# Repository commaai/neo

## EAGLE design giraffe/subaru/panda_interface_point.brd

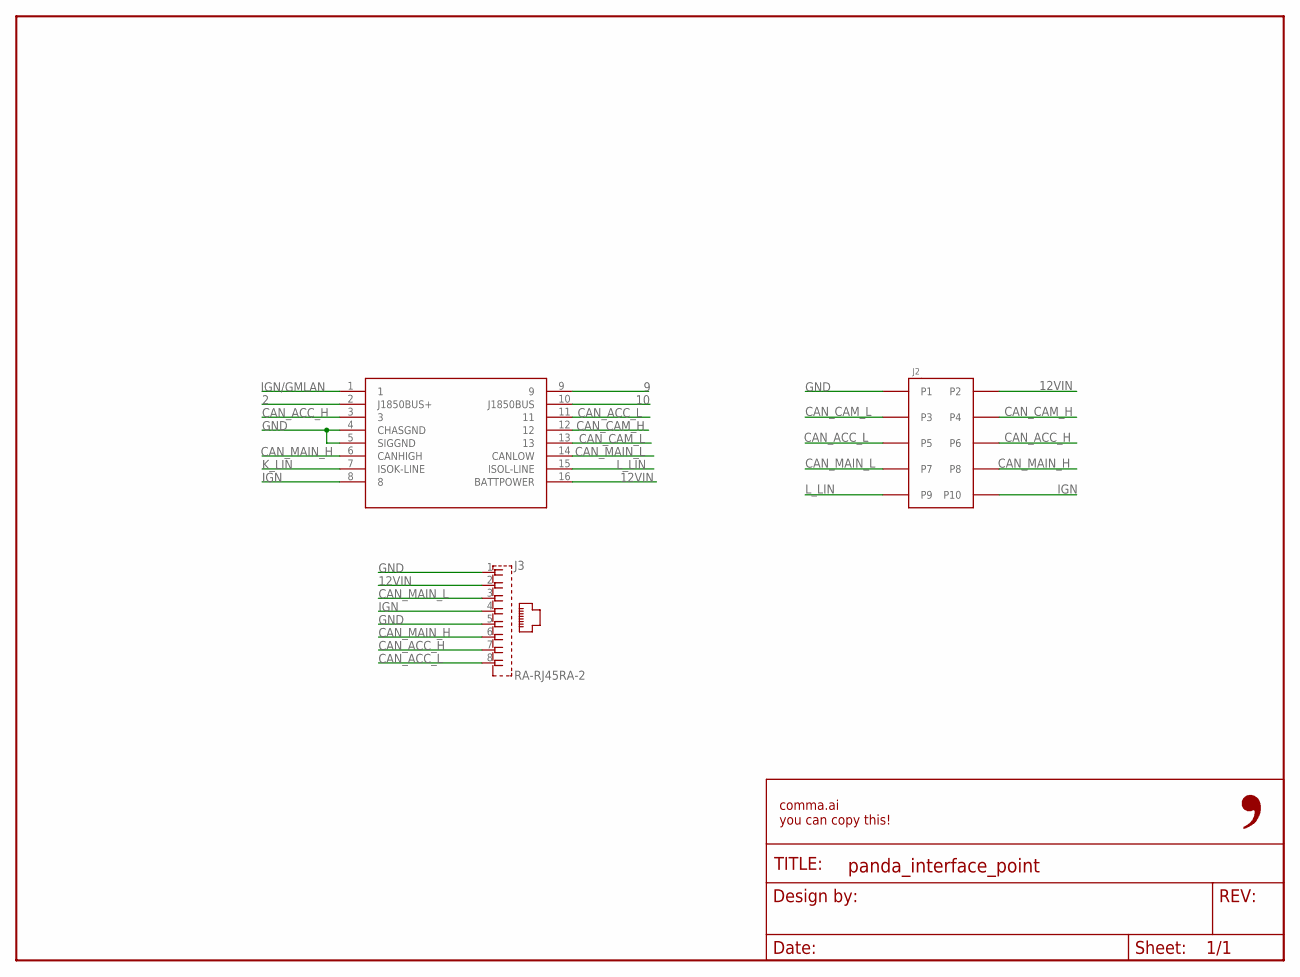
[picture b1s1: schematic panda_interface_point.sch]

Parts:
FRAME1: FRAME-LETTER-OPENNO_PACKAGE; DUMMY
J1: OBDII-FEMALE-CUT; OBDII-FEMALE-MIDCUT
J2: 5018761040
J3: RA-RJ45RA-2; RA-RJ45-2

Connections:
2: J1.2 (J1850BUS+)
9: J1.9
10: J1.10 (J1850BUS)
12VIN: J1.16 (BATTPOWER), J2.P2, J3.2
CAN_ACC_H: J1.3, J2.P6, J3.7
CAN_ACC_L: J1.11, J2.P5, J3.8
CAN_CAM_H: J1.12, J2.P4
CAN_CAM_L: J1.13, J2.P3
CAN_MAIN_H: J1.6 (CANHIGH), J2.P8, J3.6
CAN_MAIN_L: J1.14 (CANLOW), J2.P7, J3.3
GND: J1.4 (CHASGND), J1.5 (SIGGND), J2.P1, J3.1, J3.5
IGN: J1.8, J2.P10, J3.4
IGN/GMLAN: J1.1
K_LIN: J1.7 (ISOK-LINE)
L_LIN: J1.15 (ISOL-LINE), J2.P9

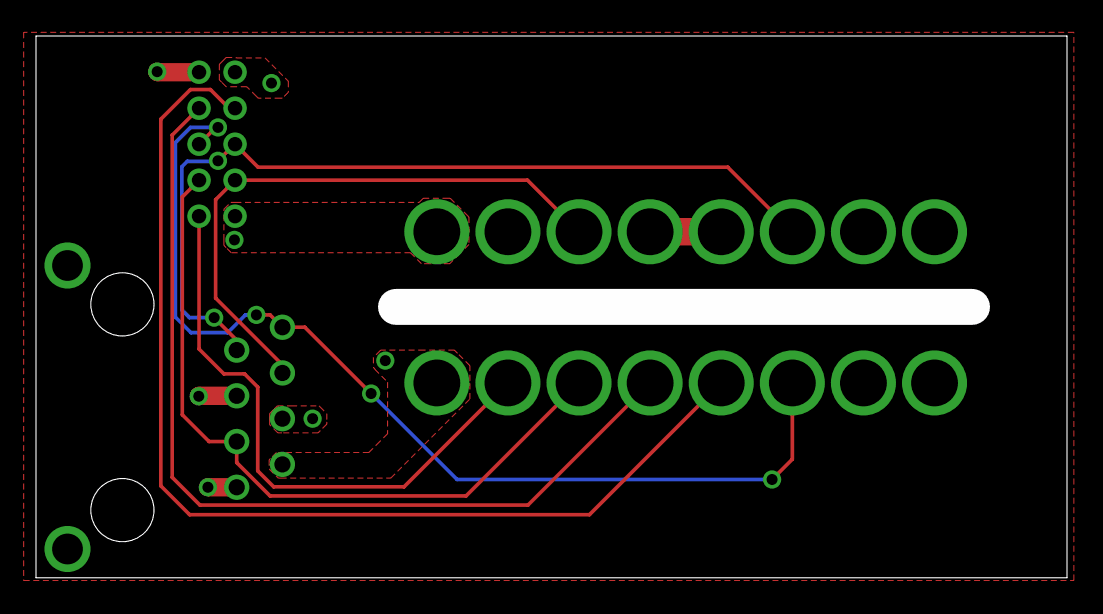
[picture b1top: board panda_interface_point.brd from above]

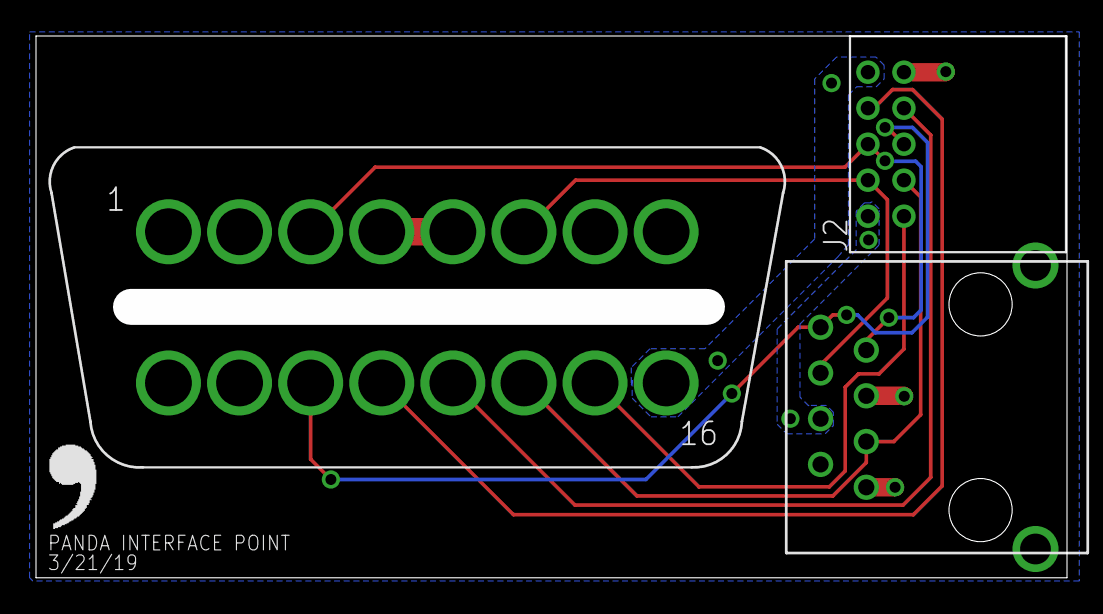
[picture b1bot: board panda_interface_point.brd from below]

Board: 2 copper layers, 57.3 x 30.1 mm, 5 parts (4 on the bottom side), 10 nets.

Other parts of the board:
U$1: LOGO

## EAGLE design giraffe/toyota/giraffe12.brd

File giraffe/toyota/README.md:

Toyota giraffe
====

Get your panda deeper into your compatible Toyota vehicle

The switches
====

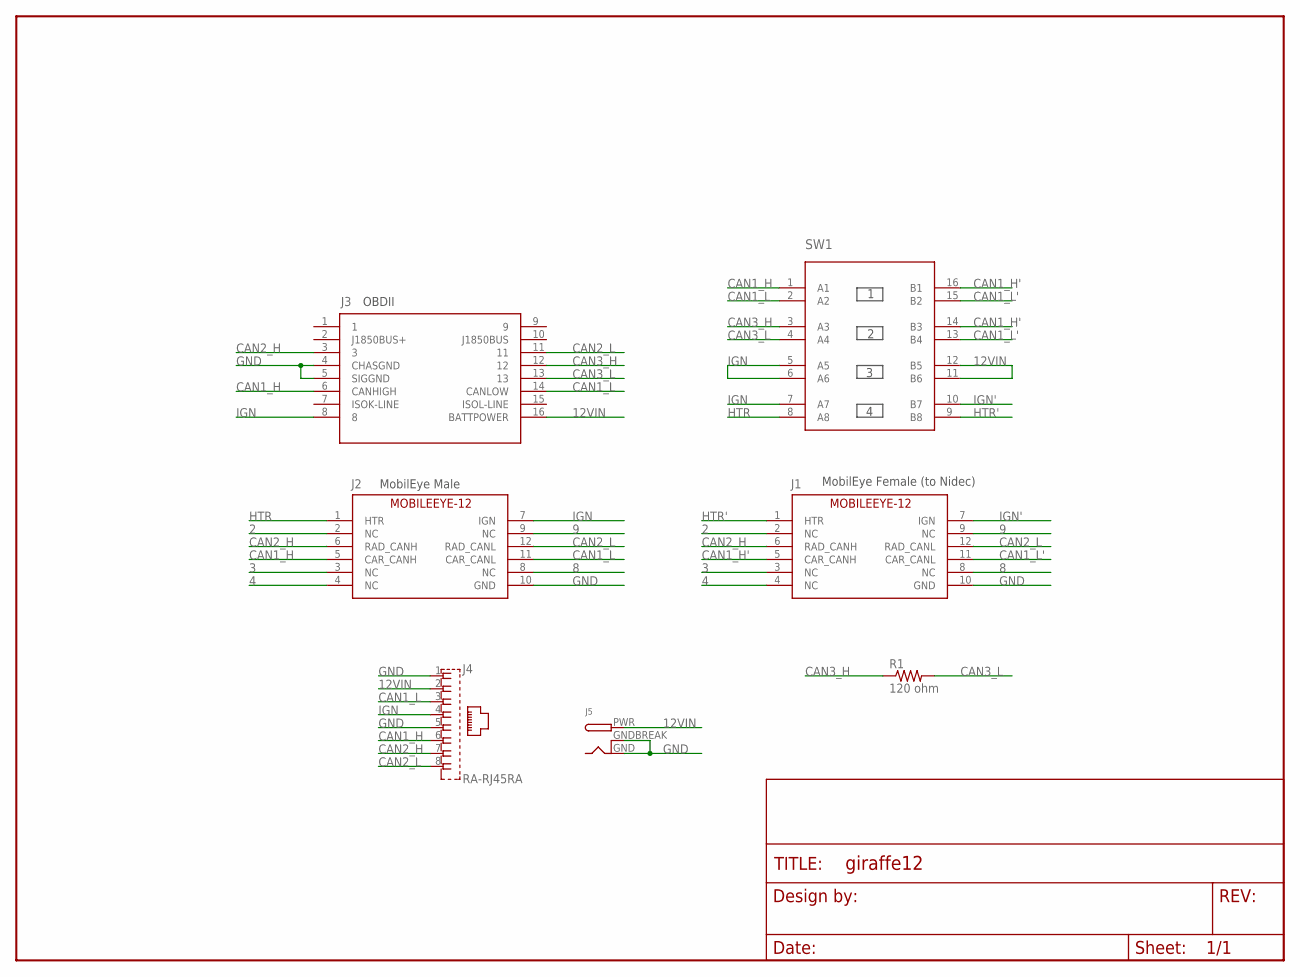
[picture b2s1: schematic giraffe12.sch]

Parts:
FRAME1: FRAME-LETTERNO_PACKAGE; DUMMY
J1: MOBILEEYE-12FEMALE; 2X6-TE-FEMALE
J2: MOBILEEYE-12MALE; 2X6-TE-RA
J3: OBDII-FEMALE-CUT; OBDII-FEMALE-MIDCUT
J4: RA-RJ45RA; RA-RJ45
J5: DCBARRELPTH; DCJACK_2MM_PTH
R1: 120 ohm; 0603-R
SW1: 4XDPSTSMT; 4-DPST

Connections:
2: J1.2 (NC), J2.2 (NC)
3: J1.3 (NC), J2.3 (NC)
4: J1.4 (NC), J2.4 (NC)
8: J1.8 (NC), J2.8 (NC)
9: J1.9 (NC), J2.9 (NC)
12VIN: J3.16 (BATTPOWER), J4.2, J5.PWR, SW1.11 (B6), SW1.12 (B5)
CAN1_H: J2.5 (CAR_CANH), J3.6 (CANHIGH), J4.6, SW1.1 (A1)
CAN1_H': J1.5 (CAR_CANH), SW1.14 (B3), SW1.16 (B1)
CAN1_L: J2.11 (CAR_CANL), J3.14 (CANLOW), J4.3, SW1.2 (A2)
CAN1_L': J1.11 (CAR_CANL), SW1.13 (B4), SW1.15 (B2)
CAN2_H: J1.6 (RAD_CANH), J2.6 (RAD_CANH), J3.3, J4.7
CAN2_L: J1.12 (RAD_CANL), J2.12 (RAD_CANL), J3.11, J4.8
CAN3_H: J3.12, R1.1, SW1.3 (A3)
CAN3_L: J3.13, R1.2, SW1.4 (A4)
GND: J1.10 (GND), J2.10 (GND), J3.4 (CHASGND), J3.5 (SIGGND), J4.1, J4.5, J5.GND, J5.GNDBREAK
HTR: J2.1 (HTR), SW1.8 (A8)
HTR': J1.1 (HTR), SW1.9 (B8)
IGN: J2.7 (IGN), J3.8, J4.4, SW1.5 (A5), SW1.6 (A6), SW1.7 (A7)
IGN': J1.7 (IGN), SW1.10 (B7)

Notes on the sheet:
OBDII
MobilEye Male
MobilEye Female (to Nidec)

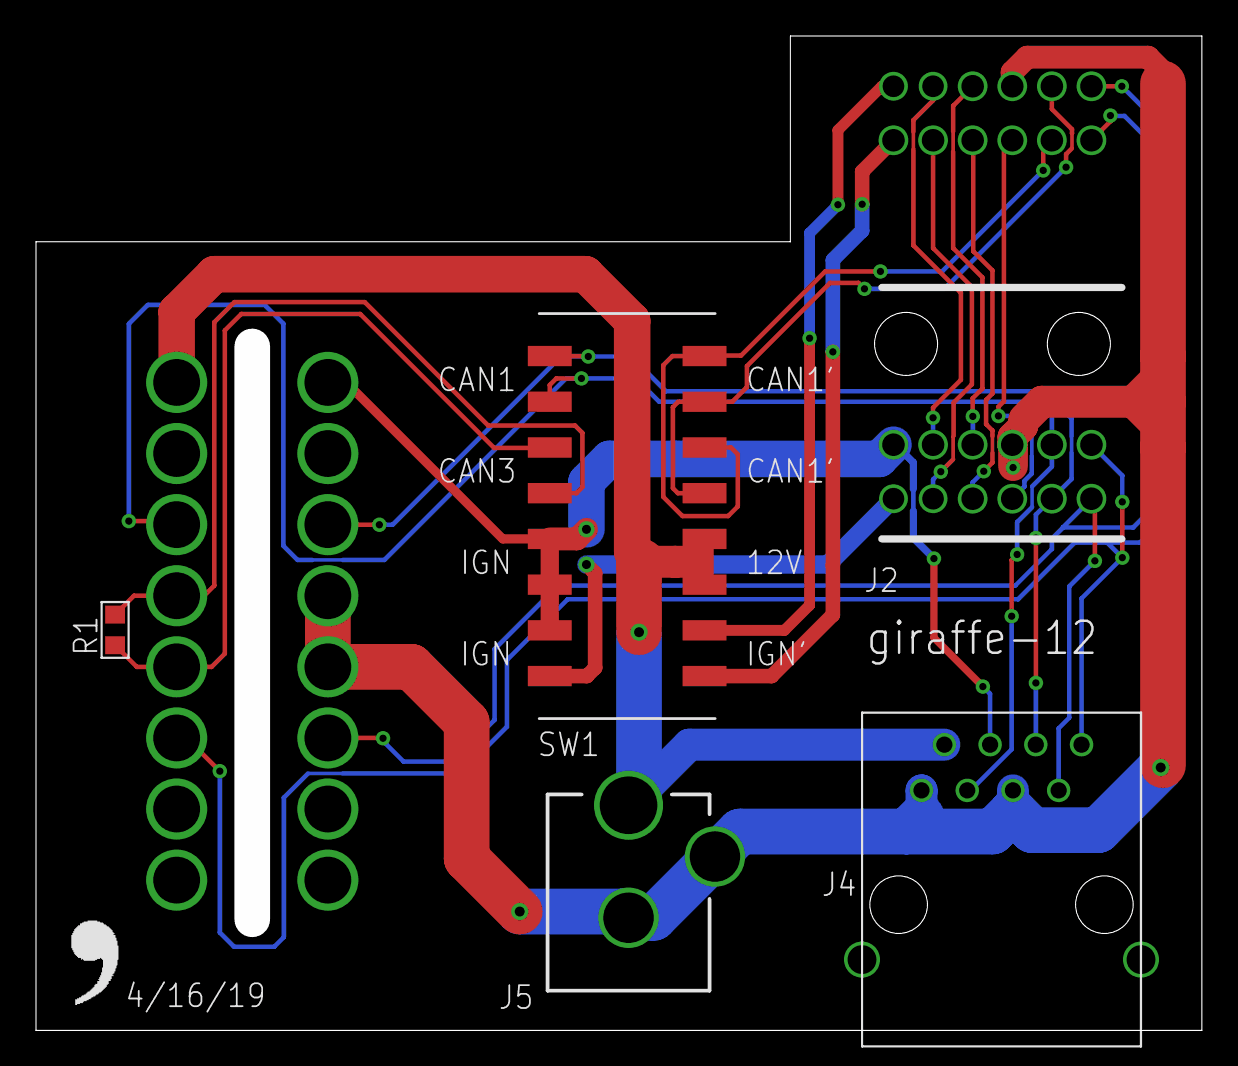
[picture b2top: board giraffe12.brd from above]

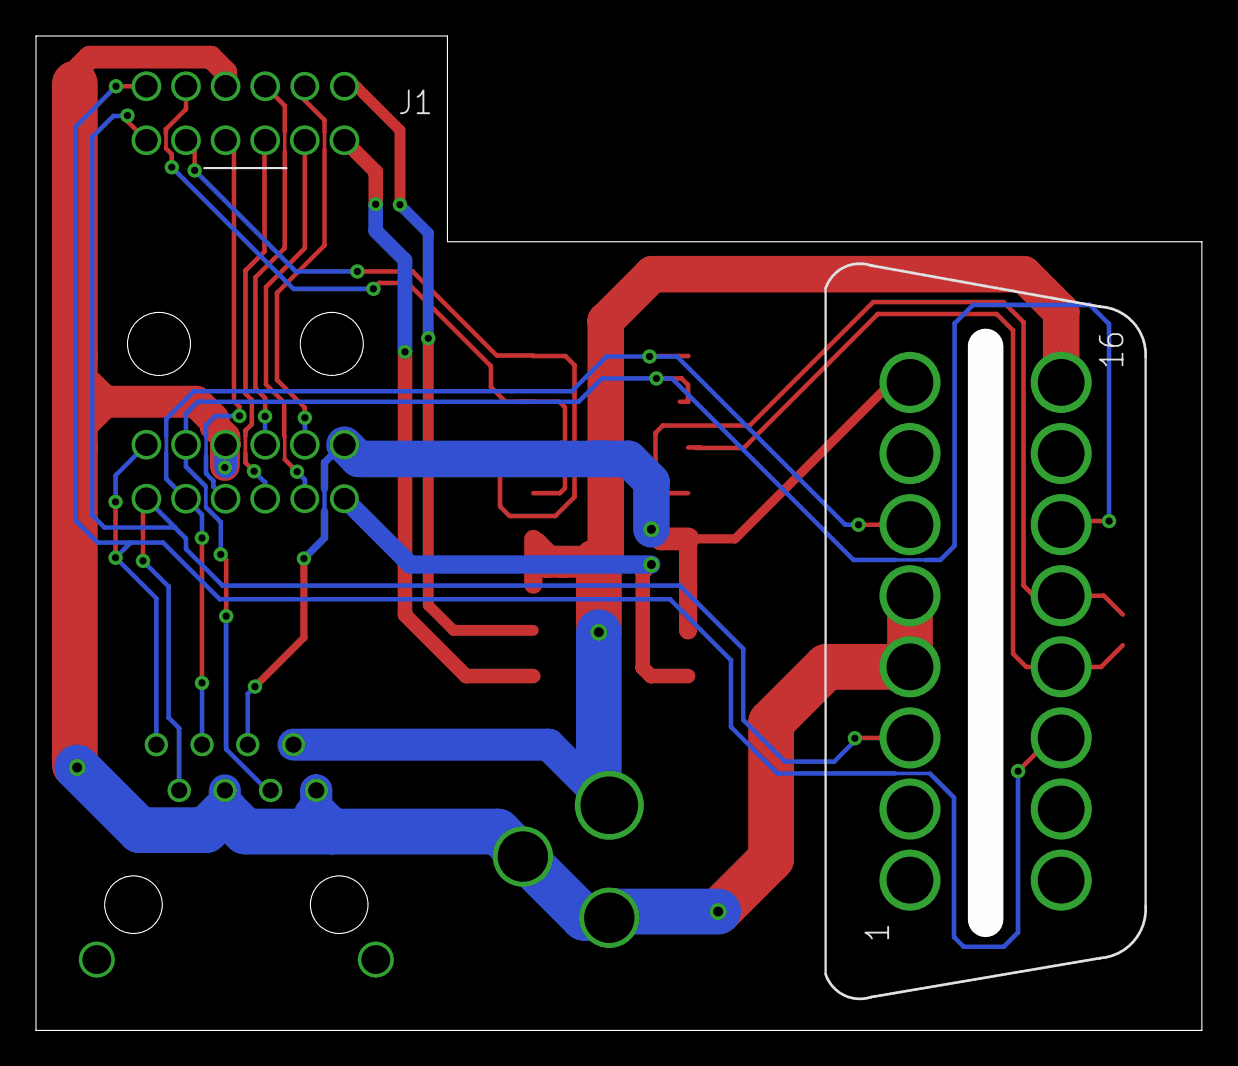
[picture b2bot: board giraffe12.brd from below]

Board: 2 copper layers, 64.8 x 55.2 mm, 9 parts (2 on the bottom side), 19 nets.

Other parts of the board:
U$1: LOGO

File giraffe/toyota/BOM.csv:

Ref Des,Package,Manufacturer PN,Qty,Link
J1,12-pin,1318774-1,1,http://www.mouser.com/Search/ProductDetail.aspx?R=1318774-1v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
J2,12-pin-RA,1318772-2,1,http://www.mouser.com/Search/ProductDetail.aspx?R=1318772-2v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
,,1123343-1,12,https://www.digikey.com/product-detail/en/te-connectivity-am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
,,PRPC040SAAN-RC,1,https://www.digikey.com/products/en?keywords=S1011EC-40-ND
J3,16-pin,OBDII-FEMALE,1,https://cn1514770021qfbj.en.alibaba.com/product/60598699808-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
J4,RJ45-RA,A-2004-2-4-LPS-N-R,1,https://www.digikey.com/product-detail/en/assmann-wsw-compon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
J5,3-pin,EJ508A,1,https://www.digikey.com/products/en?keywords=ej508a
SW1,SMD,204-214ST,1,https://www.digikey.com/scripts/DkSearch/dksus.dll?Detail&it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
R1,0603,ERJ-PA3F1200V,1,https://www.digikey.com/short/p47rhj
SCREWs,Phillips,92010A118,2,https://www.mcmaster.com/#catalog/92010A118

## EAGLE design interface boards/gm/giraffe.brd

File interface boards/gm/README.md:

GM Interface Board

====

Design from the community from: [@vntarasov](https://github.com/vntarasov)

**THIS IS ALPHA QUALITY HARDWARE, NOT TESTED, NOR DESIGNED BY COMMA.AI, FOR RESEARCH PURPOSES ONLY. THIS IS NOT A PRODUCT.
YOU ARE RESPONSIBLE FOR COMPLYING WITH LOCAL LAWS AND REGULATIONS.
NO WARRANTY EXPRESSED OR IMPLIED.**

=====

Parts for case assembly (mcmaster part numbers):
- 92010A122, M3 12mm flat head
- 94180A331, M3 heat insert

PCB parts: digikey.csv

Connector pins:
- For data pins, Digikey part # SAM12735-ND
- For power & ground pins, Mouser part # 829-15304702

Assembly steps:
- Order PCB from Oshpark and populate yourself, or order a populated PCB from Macrofab
  Solder everything except for connector headers and power pins
- Flash the board with
  - Connect 5v, ground, data+, data- to USB host. Use external 5v power
  - Don't use 5v linear regulator for USB power, it will get fried
  - Pull high (to +3.3v net) BOOT testpoint, through 1k resistor, to put board into DFU
- Print case.stl and connector.stl, use ABS filament
- Install m3 heat insert into the case
- Drill holes in the connector housing for easier insertion of data pins, from 0.7mm to 0.75mm
- Cut 0.1" connector header SAM12735-ND to 12-pin and 16-pin sizes
- Cut one of the 829-15304702 short, bend the other one 90 degrees
- Insert shorter 829-15304702 (+12v) into connector housing
  - Put enough solder on the +12v testpoint of the PCB
  - Insert 0.1" headers into PCB, then solder the +12v pin to the PCB
  - Connector's plastic is going to melt, immobilizing the +12v pin is recommended
- Solder 0.1" headers to the PCB
- Insert 90-degrees bent 829-15304702 (ground) into connector housing, solder to PCB
- Bolt down connector housing to the case

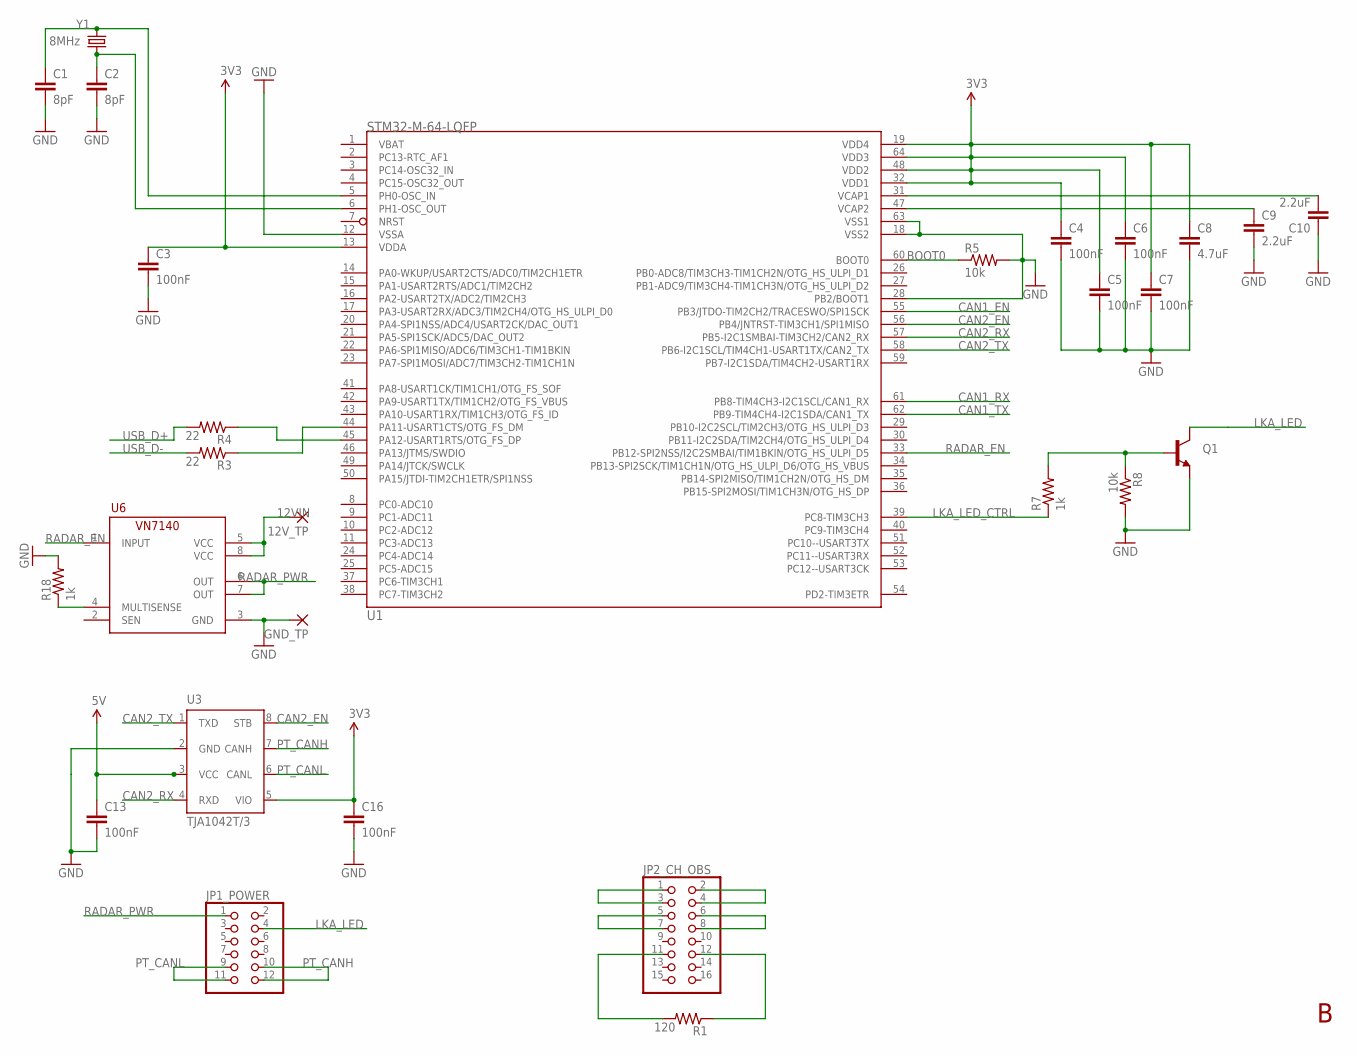
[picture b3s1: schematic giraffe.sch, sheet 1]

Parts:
12V_TP: 2,15/1,0
C1, C2: 8pF; 0603-CAP
C3, C4, C5, C6, C7, C13, C16: 100nF; 0603-CAP
C8: 4.7uF; 0603-CAP
C9, C10: 2.2uF; 0603-CAP
GND_TP: 2,15/1,0
JP1_POWER: PINHD-2X6; 2X06
JP2_CH_OBS: PINHD-2X8; 2X08
Q1: MMBT2222A; SOT23-3
R1: 120; R0603
R3, R4: 22; R0603
R5, R8: 10k; R0603
R7, R18: 1k; R0603
U1: STM32-M-64-LQFP; LQFP64
U3: TJA1042T/3; SO-8-L
U6: VN7140; SO08
Y1: 8MHz; CRYSTAL-TXC-7A

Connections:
3V3: C3.1, C4.1, C5.1, C6.1, C7.1, C8.1, C16.1, U1.13 (VDDA), U1.19 (VDD4), U1.32 (VDD1), U1.48 (VDD2), U1.64 (VDD3), U3.5 (VIO); also elsewhere on the board
5V: C13.1, U3.3 (VCC); also elsewhere on the board
12VIN: 12V_TP.1, U6.5 (VCC), U6.8 (VCC); also elsewhere on the board
BOOT0: R5.1, U1.60 (BOOT0)
CAN1_EN: U1.55 (PB3/JTDO-TIM2CH2/TRACESWO/SPI1SCK)
CAN1_RX: U1.61 (PB8-TIM4CH3-I2C1SCL/CAN1_RX)
CAN1_TX: U1.62 (PB9-TIM4CH4-I2C1SDA/CAN1_TX)
CAN2_EN: U1.56 (PB4/JNTRST-TIM3CH1/SPI1MISO), U3.8 (STB)
CAN2_RX: U1.57 (PB5-I2C1SMBAI-TIM3CH2/CAN2_RX), U3.4 (RXD)
CAN2_TX: U1.58 (PB6-I2C1SCL/TIM4CH1-USART1TX/CAN2_TX), U3.1 (TXD)
GND: C1.2, C2.2, C3.2, C4.2, C5.2, C6.2, C7.2, C8.2, C9.2, C10.1, C13.2, C16.2, GND_TP.1, Q1.2 (E), R5.2, R8.2, R18.2, U1.12 (VSSA), U1.18 (VSS2), U1.28 (PB2/BOOT1), U1.63 (VSS1), U3.2 (GND), U6.3 (GND); also elsewhere on the board
LKA_LED: JP1_POWER.4, Q1.3 (C)
LKA_LED_CTRL: R7.1, U1.39 (PC8-TIM3CH3)
unnamed: C1.1, U1.5 (PH0-OSC_IN), Y1.P$1 (1)
unnamed: JP2_CH_OBS.2, JP2_CH_OBS.4
unnamed: C2.1, U1.6 (PH1-OSC_OUT), Y1.P$2 (2)
unnamed: R4.1, U1.45 (PA12-USART1RTS/OTG_FS_DP)
unnamed: JP2_CH_OBS.1, JP2_CH_OBS.3
unnamed: Q1.1 (B), R7.2, R8.1
unnamed: JP2_CH_OBS.6, JP2_CH_OBS.8
unnamed: JP2_CH_OBS.5, JP2_CH_OBS.7
unnamed: R18.1, U6.4 (MULTISENSE)
unnamed: JP2_CH_OBS.11, R1.2
unnamed: JP2_CH_OBS.12, R1.1
unnamed: R3.1, U1.44 (PA11-USART1CTS/OTG_FS_DM)
PT_CANH: JP1_POWER.10, JP1_POWER.12, U3.7 (CANH)
PT_CANL: JP1_POWER.9, JP1_POWER.11, U3.6 (CANL)
RADAR_EN: U1.33 (PB12-SPI2NSS/I2C2SMBAI/TIM1BKIN/OTG_HS_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), U6.1 (INPUT)
RADAR_PWR: JP1_POWER.1, U6.6 (OUT), U6.7 (OUT)
USB_D+: R4.2
USB_D-: R3.2
VCAP1: C10.2, U1.31 (VCAP1)
VCAP2: C9.1, U1.47 (VCAP2)

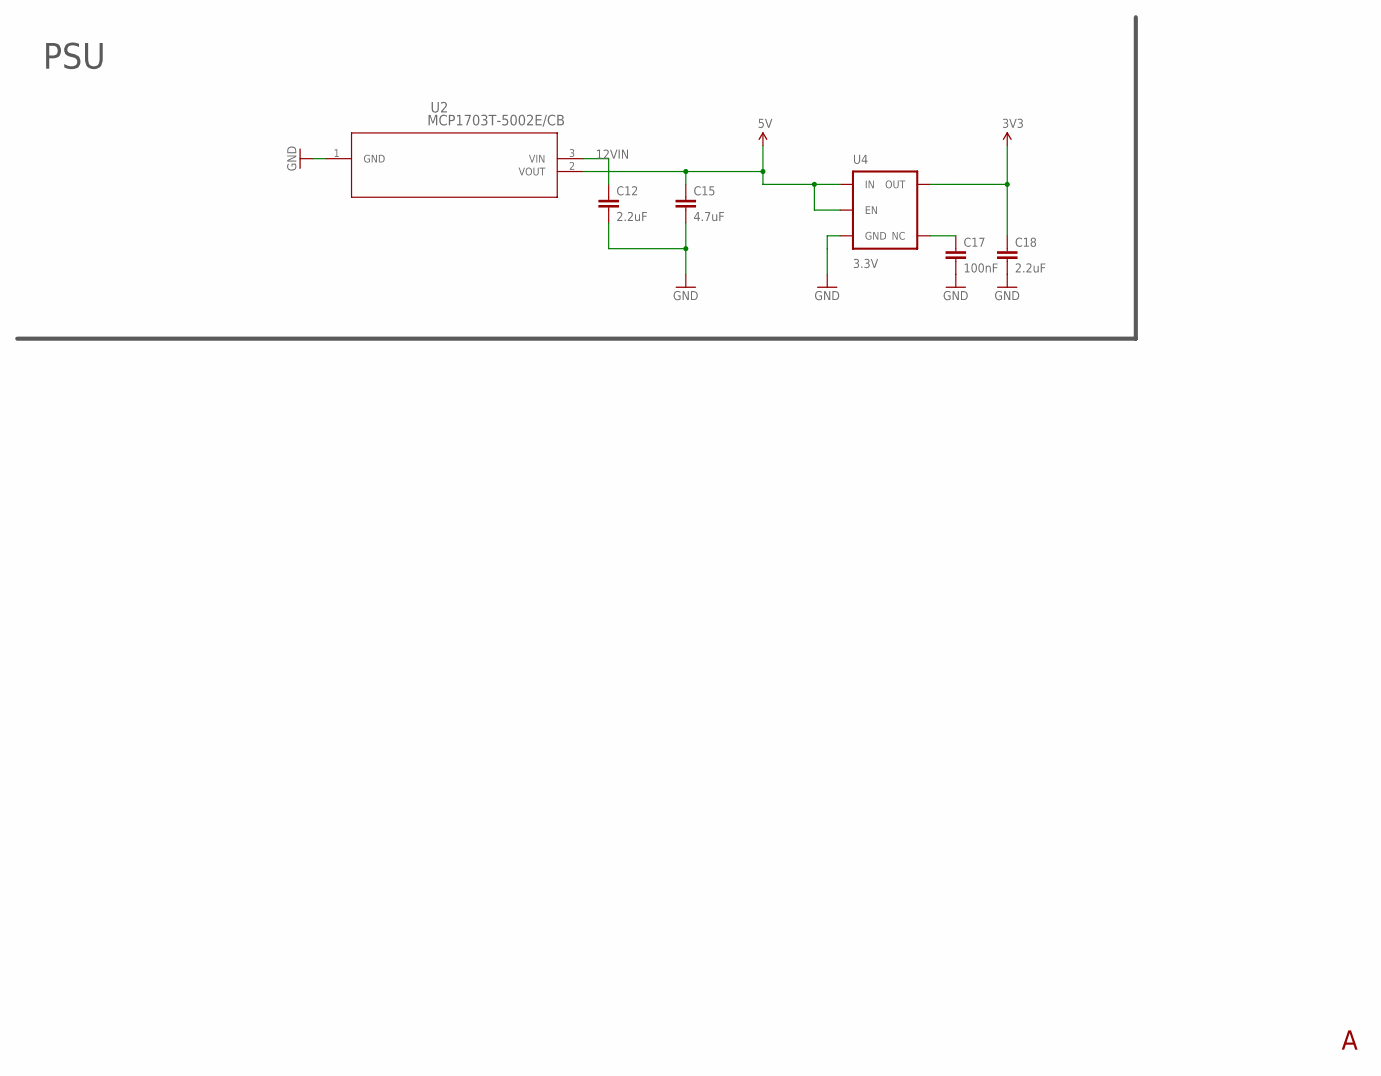
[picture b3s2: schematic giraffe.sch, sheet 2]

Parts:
C12: 2.2uF; 0805-CAP
C15: 4.7uF; 0603-CAP
C17: 100nF; 0603-CAP
C18: 2.2uF; 0603-CAP
U2: MCP1703T-5002E/CB; SOT-23A_MC
U4: 3.3V; SOT23-5

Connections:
3V3: C18.1, U4.5 (OUT); also elsewhere on the board
5V: C15.1, U2.2 (VOUT), U4.1 (IN), U4.3 (EN); also elsewhere on the board
12VIN: C12.1, U2.3 (VIN); also elsewhere on the board
GND: C12.2, C15.2, C17.2, C18.2, U2.1 (GND), U4.2 (GND); also elsewhere on the board
unnamed: C17.1, U4.4 (NC)

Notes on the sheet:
PSU

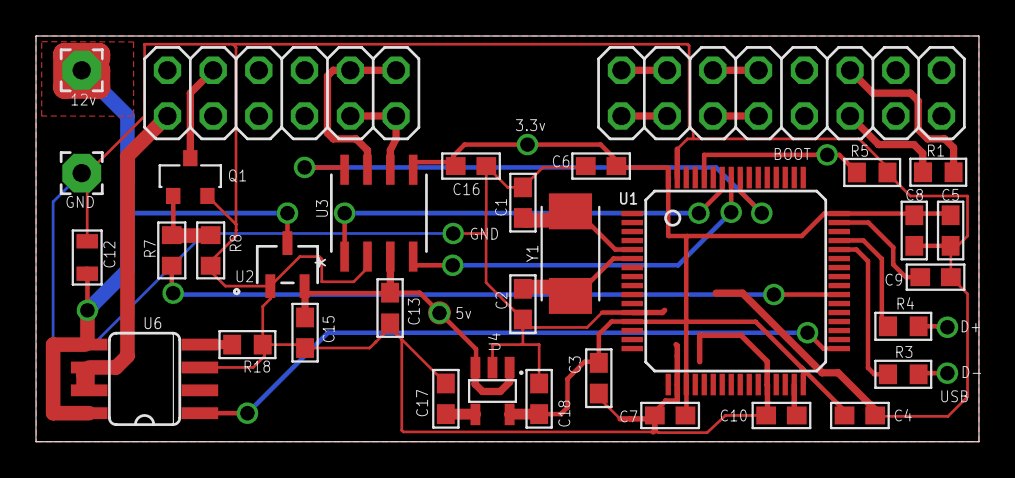
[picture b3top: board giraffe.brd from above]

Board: 2 copper layers, 52.4 x 22.5 mm, 34 parts (0 on the bottom side), 29 nets.

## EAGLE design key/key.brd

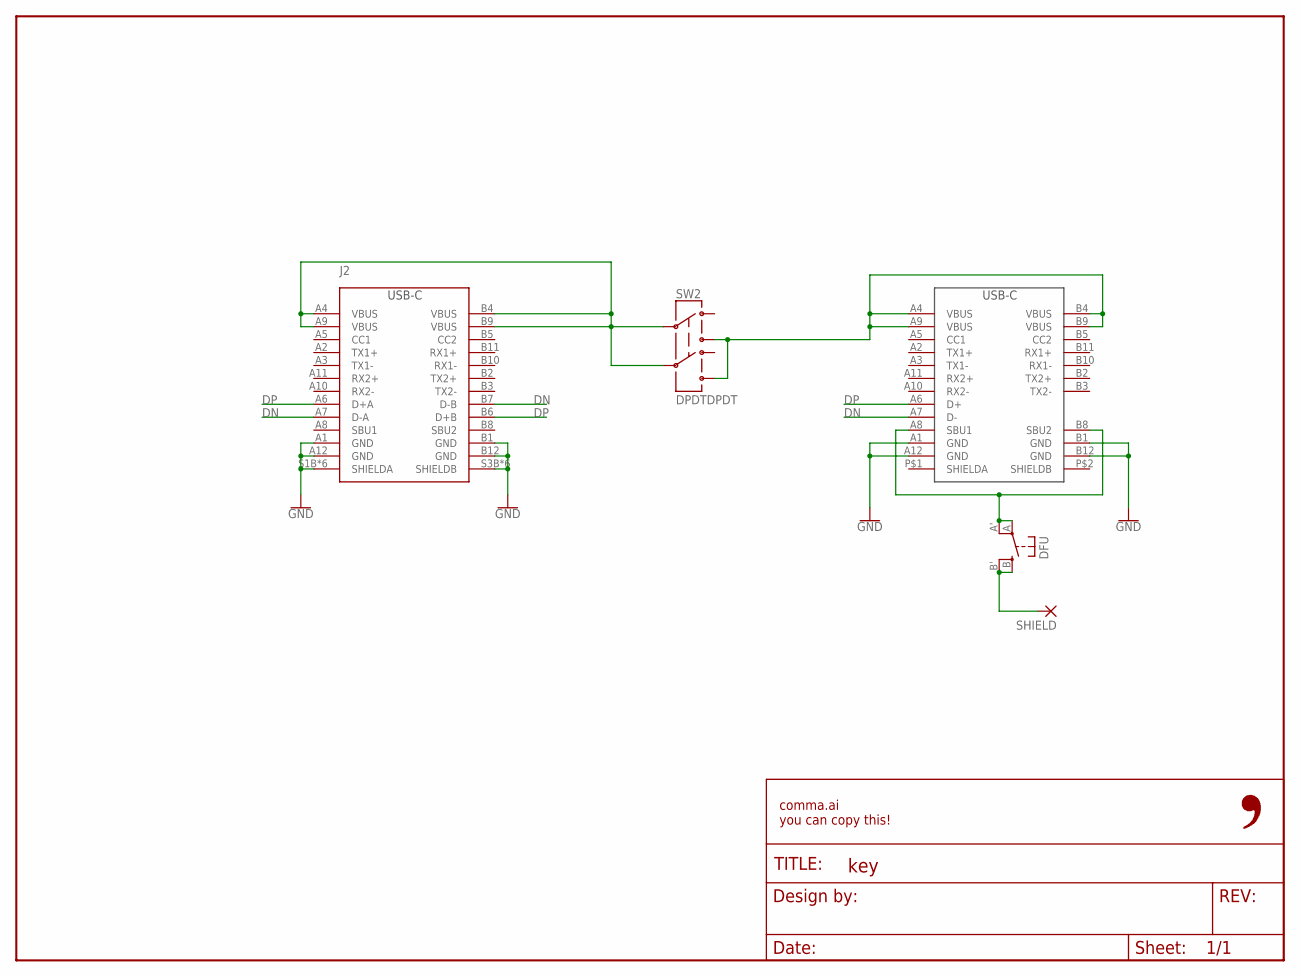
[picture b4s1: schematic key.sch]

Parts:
DFU: SPST-2-4PIN; EVQ-Q2; MPN EVQ-Q2Y03W
FRAME1: FRAME-LETTER-OPENNO_PACKAGE; DUMMY
J1: USB-C; MPN 10544440001
J2: USB-C-FEMALE; DX07S024XJ1R1100; MPN DX07S024XJ1R1100
SHIELD: 1,6/0,8
SW2: DPDTDPDT; AYZ0202; MPN JS202011SCQN

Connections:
DN: J1.A7 (D-), J2.A7 (D-A), J2.B7 (D-B)
DP: J1.A6 (D+), J2.A6 (D+A), J2.B6 (D+B)
GND: J1.A1 (GND), J1.A12 (GND), J1.B1 (GND), J1.B12 (GND), J2.A1 (GND), J2.A12 (GND), J2.B1 (GND), J2.B12 (GND), J2.S1B (SHIELDA), J2.S1T (SHIELDA), J2.S1TH (SHIELDA), J2.S2B (SHIELDA), J2.S2T (SHIELDA), J2.S2TH (SHIELDA), J2.S3B (SHIELDB), J2.S3T (SHIELDB), J2.S3TH (SHIELDB), J2.S4B (SHIELDB), J2.S4T (SHIELDB), J2.S4TH (SHIELDB)
unnamed: J1.A4 (VBUS), J1.A9 (VBUS), J1.B4 (VBUS), J1.B9 (VBUS), SW2.3, SW2.6
unnamed: DFU.A, DFU.A' (P1), J1.A8 (SBU1), J1.B8 (SBU2)
unnamed: DFU.B (S), DFU.B' (S1), SHIELD.1
unnamed: J2.A4 (VBUS), J2.A9 (VBUS), J2.B4 (VBUS), J2.B9 (VBUS), SW2.2, SW2.5

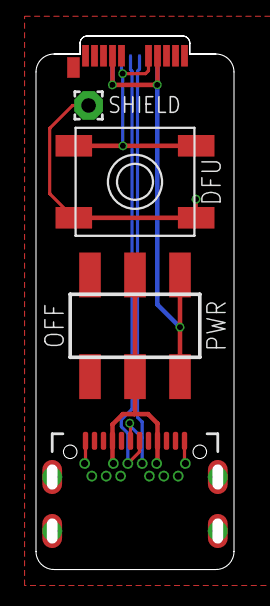
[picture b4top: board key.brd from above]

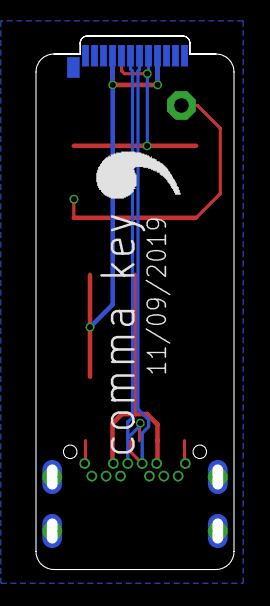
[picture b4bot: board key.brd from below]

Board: 2 copper layers, 11.0 x 29.6 mm, 7 parts (2 on the bottom side), 7 nets.

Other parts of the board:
U$1: LOGO

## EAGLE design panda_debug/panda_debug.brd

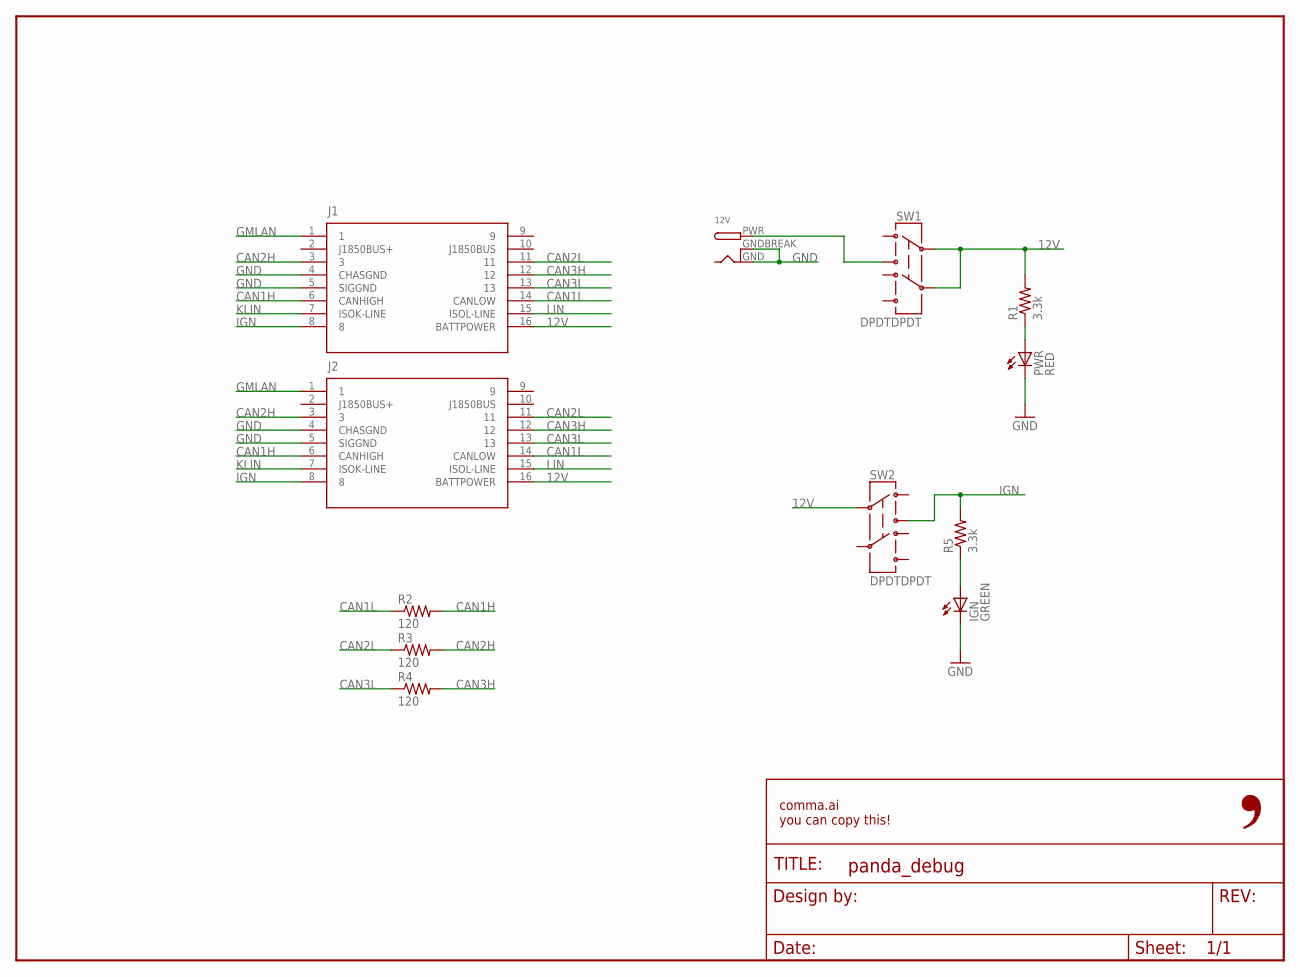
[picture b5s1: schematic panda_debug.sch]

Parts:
12V: DCBARRELPTH; DCJACK_2MM_PTH
FRAME1: FRAME-LETTER-OPENNO_PACKAGE; DUMMY
IGN: GREEN; CHIPLED_0805
J1, J2: OBDII-FEMALEFEMALE; OBDII-FEMALE
PWR: RED; CHIPLED_0805
R1, R5: 3.3k; 0603-R
R2, R3, R4: 120; 0603-R
SW1, SW2: DPDTDPDT; AYZ0202

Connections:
12V: J1.16 (BATTPOWER), J2.16 (BATTPOWER), R1.2, SW1.2, SW1.5, SW2.2
CAN1H: J1.6 (CANHIGH), J2.6 (CANHIGH), R2.2
CAN1L: J1.14 (CANLOW), J2.14 (CANLOW), R2.1
CAN2H: J1.3, J2.3, R3.2
CAN2L: J1.11, J2.11, R3.1
CAN3H: J1.12, J2.12, R4.2
CAN3L: J1.13, J2.13, R4.1
GMLAN: J1.1, J2.1
GND: 12V.GND, 12V.GNDBREAK, IGN.C, J1.4 (CHASGND), J1.5 (SIGGND), J2.4 (CHASGND), J2.5 (SIGGND), PWR.C
IGN: J1.8, J2.8, R5.2, SW2.3
KLIN: J1.7 (ISOK-LINE), J2.7 (ISOK-LINE)
LIN: J1.15 (ISOL-LINE), J2.15 (ISOL-LINE)
unnamed: 12V.PWR, SW1.3
unnamed: PWR.A, R1.1
unnamed: IGN.A, R5.1

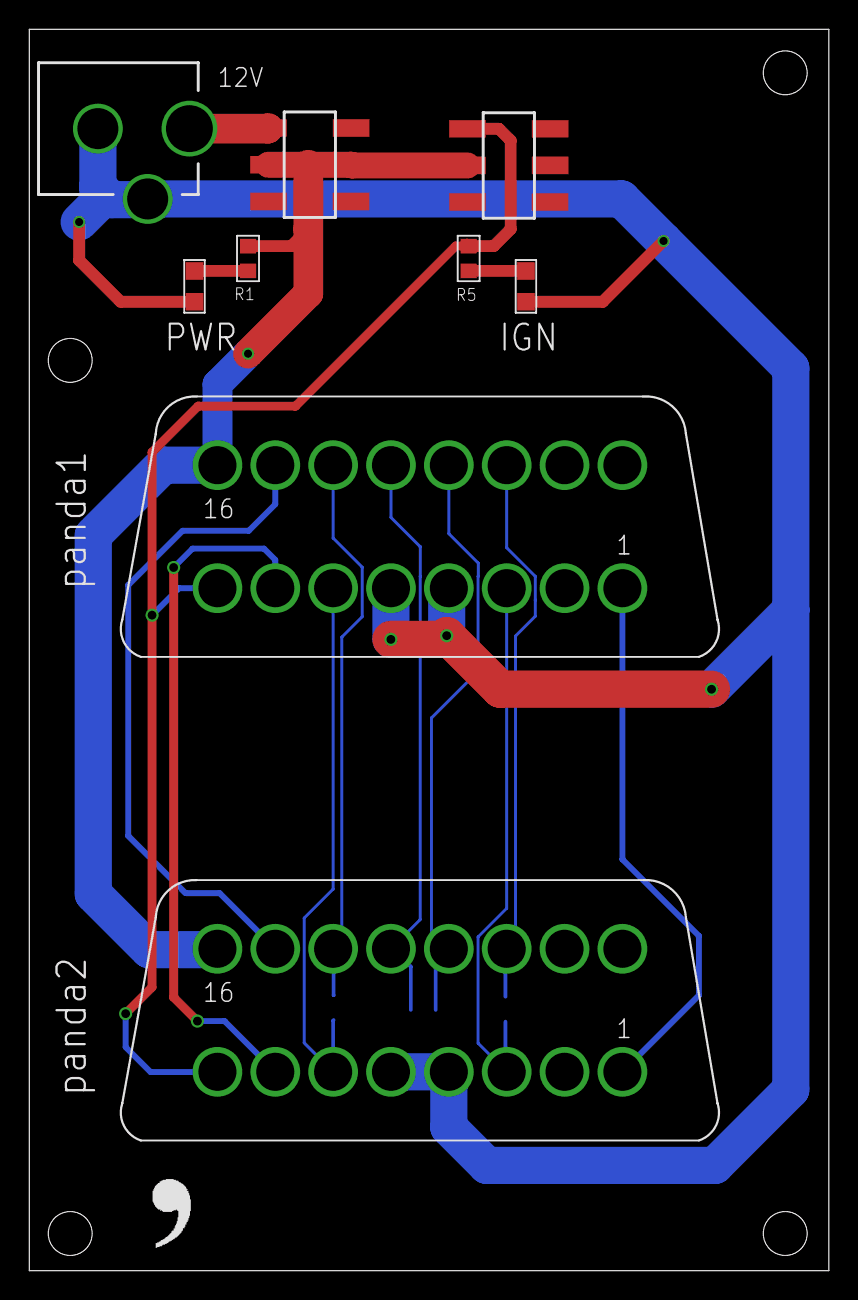
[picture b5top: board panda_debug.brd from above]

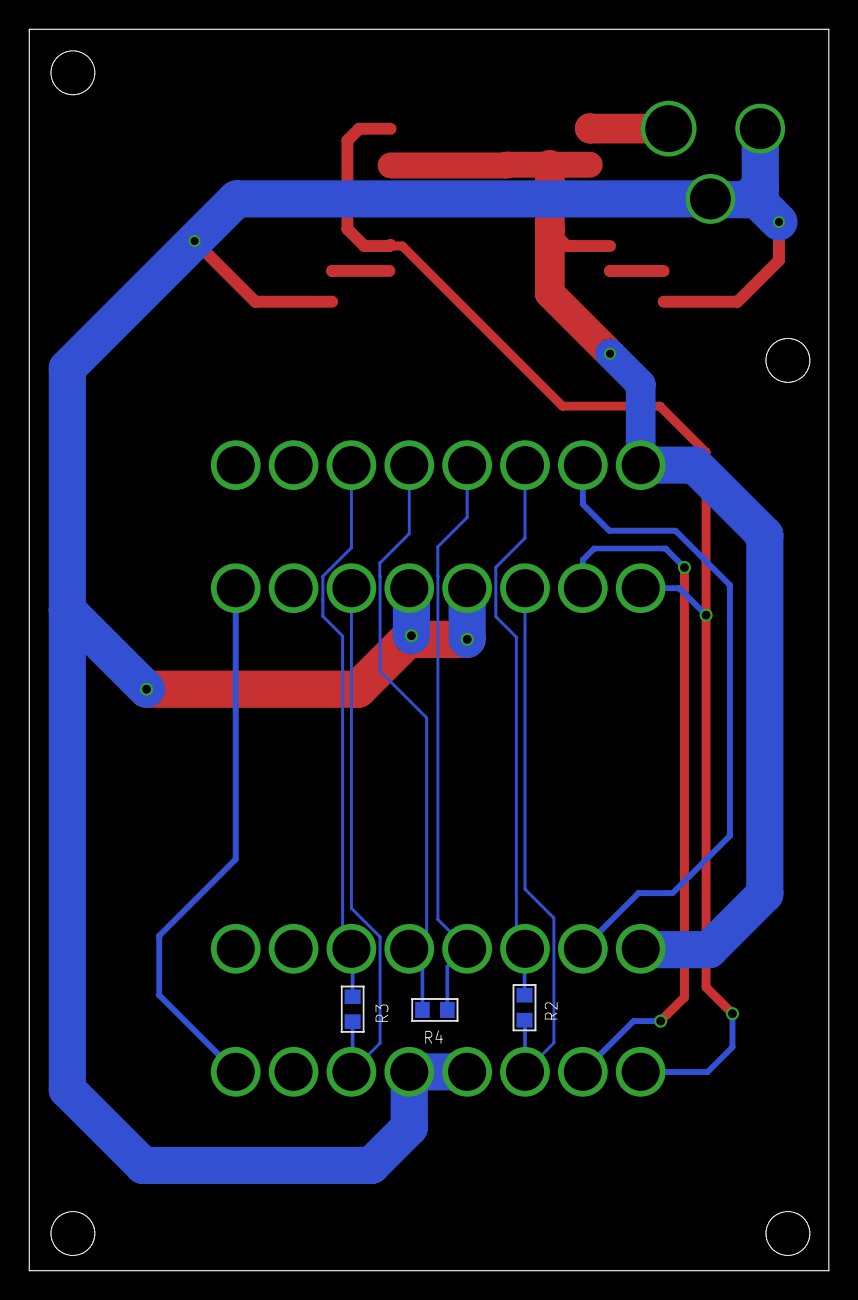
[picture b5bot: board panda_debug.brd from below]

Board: 2 copper layers, 54.6 x 84.8 mm, 14 parts (3 on the bottom side), 15 nets.

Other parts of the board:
U$1: LOGO

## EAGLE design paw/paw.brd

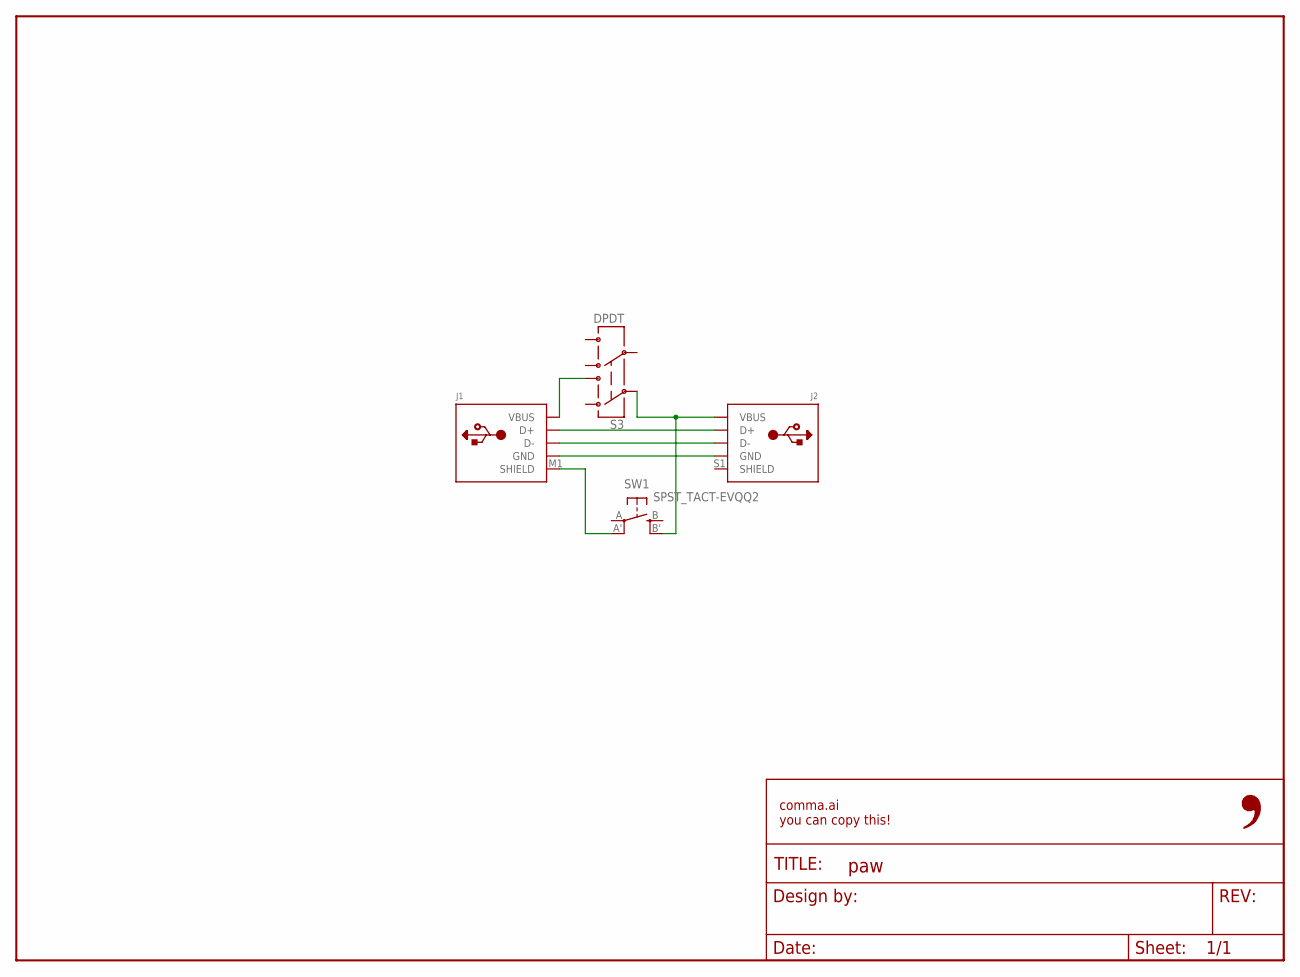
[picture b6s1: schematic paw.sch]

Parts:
FRAME1: FRAME-LETTER-OPENNO_PACKAGE; DUMMY
J1: USB-AA-M; MOLEX_480371000
J2: USB-MINIBSMD; USB-MINIB
S3: DPDT; AYZ0202
SW1: SPST_TACT-EVQQ2; EVQ-Q2

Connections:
unnamed: J1.3 (D+), J2.D+
unnamed: J1.2 (D-), J2.D-
unnamed: J1.4 (GND), J2.GND
unnamed: J1.M1 (SHIELD), SW1.A' (P1)
unnamed: J1.1 (VBUS), S3.3
unnamed: J2.VBUS, S3.2, SW1.B' (S1)

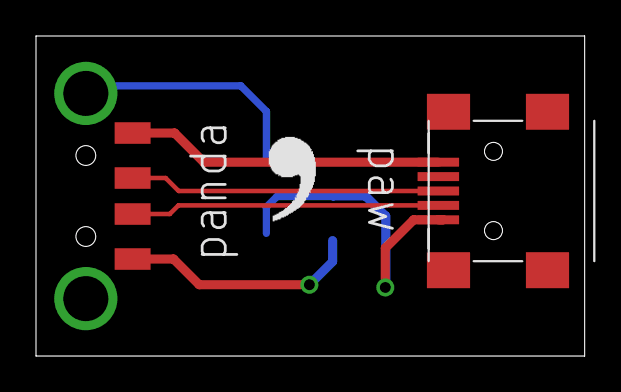
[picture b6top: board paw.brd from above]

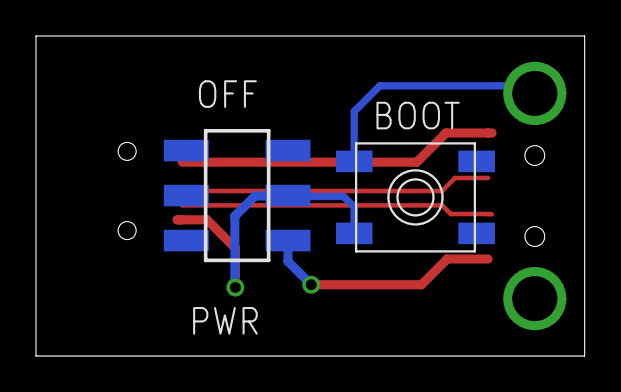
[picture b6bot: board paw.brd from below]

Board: 2 copper layers, 30.5 x 17.8 mm, 6 parts (2 on the bottom side), 6 nets.

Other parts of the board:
U$1: LOGO

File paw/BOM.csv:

Ref Des,Package,Value,Manufacturer PN,Qty
S3,DPDT,DPDTDPDT,JS202011SCQN,1
SW1,SPST_TACT-EVQQ2,SPST_TACT-EVQQ2,EVQ-Q2Y03W,1
X1,USB-AA-M,USB-AA-M,1001-011-01101,1
J2,USB-MINIBSMD,USB-MINIBSMD,10033526-N3212LF,1

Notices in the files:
parts and their libraries:
SparkFun-Aesthetics: Licensing: Creative Commons ShareAlike 4.0 International - https://creativecommons.org/licenses/by-sa/4.0
SparkFun-Aesthetics: Released under the Creative Commons Attribution Share-Alike 4.0 License
SparkFun-Aesthetics: https://creativecommons.org/licenses/by-sa/4.0
